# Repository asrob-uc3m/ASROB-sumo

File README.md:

# ASROB-sumo
Robot sumo de RoboFactory

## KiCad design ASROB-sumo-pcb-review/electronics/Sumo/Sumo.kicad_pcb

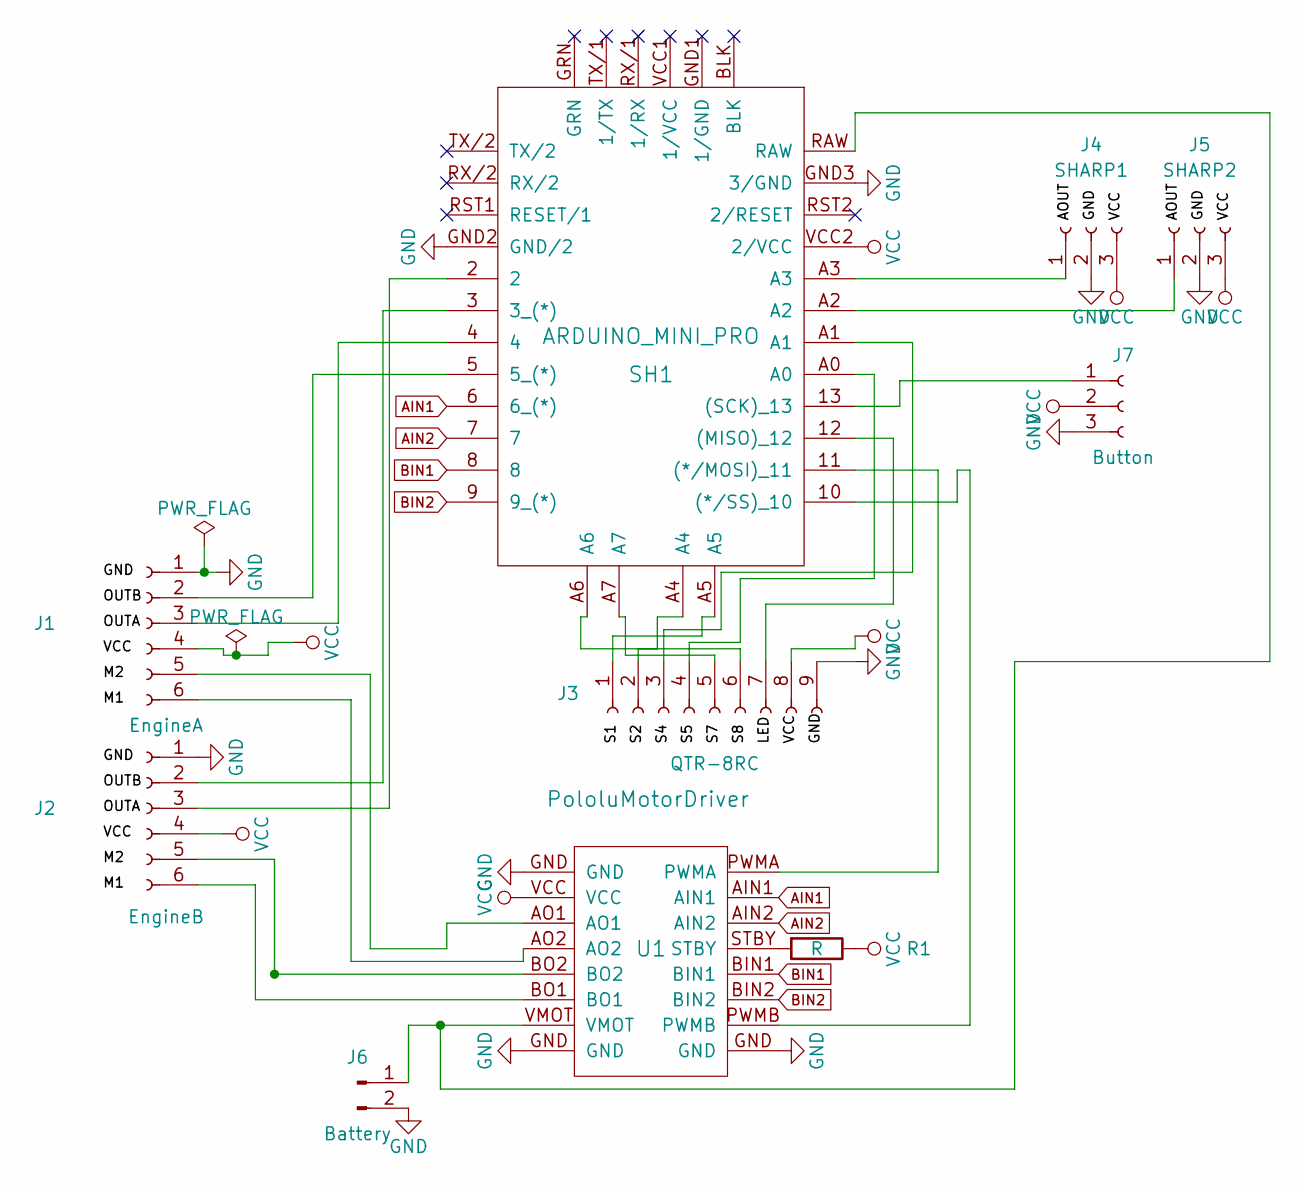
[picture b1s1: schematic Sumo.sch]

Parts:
J1: EngineA; Socket_Strip_Straight_1x06_Pitch2.54mm
J2: EngineB; Socket_Strip_Straight_1x06_Pitch2.54mm
J3: QTR-8RC; Socket_Strip_Straight_1x09_Pitch2.54mm
J4: SHARP1; Socket_Strip_Straight_1x03_Pitch2.54mm
J5: SHARP2; Socket_Strip_Straight_1x03_Pitch2.54mm
J6: Battery; Pin_Header_Straight_1x02_Pitch2.54mm
J7: Button; Socket_Strip_Straight_1x03_Pitch2.54mm
R1: R; R_Axial_DIN0204_L3.6mm_D1.6mm_P5.08mm_Horizontal
SH1: ARDUINO_MINI_PRO; ARDUINO_MINI_PRO_V10
U1: PololuMotorDriver

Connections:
AIN1: SH1.6 (6_(*)), U1.AIN1
AIN2: SH1.7, U1.AIN2
BIN1: SH1.8, U1.BIN1
BIN2: SH1.9 (9_(*)), U1.BIN2
GND: J1.1, J2.1, J3.9, J4.2, J5.2, J6.2, J7.3, SH1.GND2 (GND/2), SH1.GND3 (3/GND), U1.GND
unnamed: J1.2, SH1.5 (5_(*))
unnamed: J1.3, SH1.4
unnamed: J1.5, U1.AO1
unnamed: J1.6, U1.AO2
unnamed: J2.2, SH1.3 (3_(*))
unnamed: J2.3, SH1.2
unnamed: J2.5, U1.BO2
unnamed: J2.6, U1.BO1
unnamed: J3.1, SH1.A5
unnamed: J3.2, SH1.A4
unnamed: J3.3, SH1.A1
unnamed: J3.4, SH1.A0
unnamed: J3.5, SH1.A7
unnamed: J3.6, SH1.A6
unnamed: J3.7, SH1.12 ((MISO)_12)
unnamed: J4.1, SH1.A3
unnamed: J5.1, SH1.A2
unnamed: J6.1, SH1.RAW, U1.VMOT
unnamed: J7.1, SH1.13 ((SCK)_13)
unnamed: R1.2, U1.STBY
unnamed: SH1.10 ((*/SS)_10), U1.PWMB
unnamed: SH1.11 ((*/MOSI)_11), U1.PWMA
VCC: J1.4, J2.4, J3.8, J4.3, J5.3, J7.2, R1.1, SH1.VCC2 (2/VCC), U1.VCC

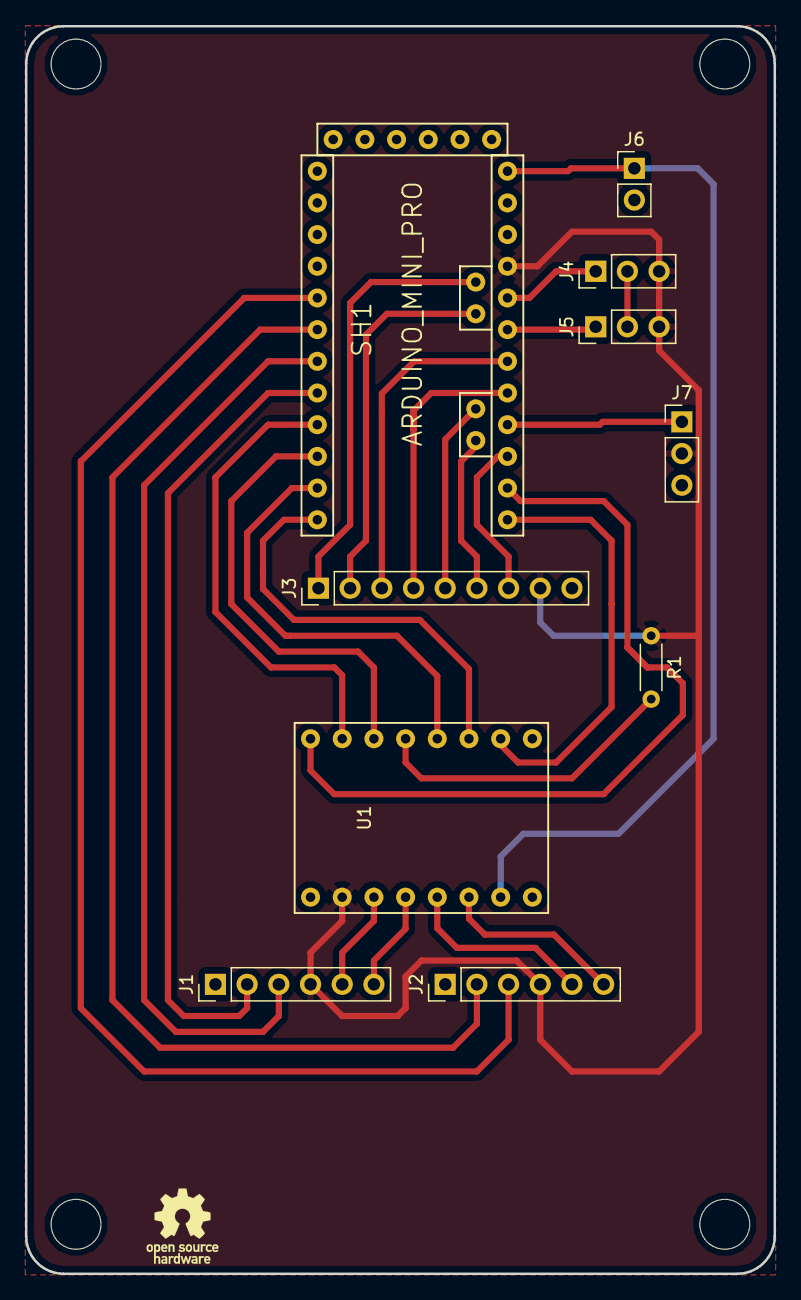
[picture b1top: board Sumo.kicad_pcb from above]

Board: 2 copper layers, 60.0 x 100.0 mm, 10 parts (0 on the bottom side), 28 nets.

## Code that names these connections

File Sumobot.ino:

#include <QTRSensors.h>
#define NUM_SENSORS 4
#define TIMEOUT 2500
#define EMITTER_PIN 8

QTRSensorsRC qtrrc((unsigned char[]) {A4, A3, A2, A1},
  NUM_SENSORS, TIMEOUT, EMITTER_PIN); 
unsigned int sensorValues[NUM_SENSORS];

int SH1 = A0;
int SH2 = A5;
int QTR1 = A1;
int QTR4 = A2;
int QTR5 = A3;
int QTR8 = A4;
int Bin1 = 5;
int Bin2 = 6;
int Ain1 = 11;
int Ain2 = 12;
int PwmA = 10;
int PwmB = 9;
int Button = 7;

void setup() {
  delay(500);
  pinMode(13, OUTPUT);
  digitalWrite(13, HIGH);
  for (int i = 0; i < 200; i++) 
  {
    qtrrc.calibrate();
  }
  digitalWrite(13, LOW);
  
  pinMode(Button, INPUT);
  pinMode(Bin1, OUTPUT);
  pinMode(Bin2, OUTPUT);
  pinMode(Ain1, OUTPUT);
  pinMode(Ain2, OUTPUT);
  pinMode(PwmA, OUTPUT);
  pinMode(PwmB, OUTPUT);
  Serial.begin(9600);
}
void loop() {
  int a=0, detect=0;
  if(digitalRead(Button)==LOW){
    a=1;
    delay(1000);//The delay before starting the programme, takes value 5000 in the final version
  }
  while(a==1){
    delay(1000);
    unsigned int place = qtrrc.readLine(sensorValues);
    int D1=0;
    int D2=0;
    for(int i=0; i<10; i++){
      D1=D1+analogRead(SH1);
      D2=D2+analogRead(SH2);
    }
    D1=D1/10;
    D2=D2/10;
    /*Serial.print(D1);
    Serial.print('\t');
    Serial.print(D2);
    for(int i=0;i<NUM_SENSORS;i++){
      Serial.print('\t');
      Serial.print(sensorValues[i]);
    }
    Serial.println();
    This is just to print in the serial monitor the values of the sharp sensors and the QTR's*/
    if(D1<150&&D2<150){
      spin();
    }
    else if(D1>=150&&D2>=300){
      forth();
    }
    else if(D1>=150){
      turn_left_fast();
      delay(50);
    }
    else if(D2>=150){
      turn_right_fast();
      delay(50);
    }
    /*else if(sensorValues[0]<Value&&sensorValues[3]){
     * back();
     * delay(500);
     * turn_left();
     * delay(500);
     * }
     * else if(sensorValues[0]<Value){
     *   turn_left();
     *   delay(500);
     * }
     * else if(sensorValues[3]<Value){
     *   turn_right();
     *   delay(500);
     * }
     */
  }
}

void no_motion(){
      analogWrite(PwmA, 0);
      analogWrite(PwmB, 0);
      digitalWrite(Ain1, LOW);
      digitalWrite(Ain2, LOW);
      digitalWrite(Bin1, LOW);
      digitalWrite(Bin2, LOW);
}
void fast_detention(){
      analogWrite(PwmA, 0);
      analogWrite(PwmB, 0);
      digitalWrite(Ain1, HIGH);
      digitalWrite(Ain2, HIGH);
      digitalWrite(Bin1, HIGH);
      digitalWrite(Bin2, HIGH);
}
void forth(){
      analogWrite(PwmA, 230);
      analogWrite(PwmB, 230);
      digitalWrite(Ain1, HIGH);
      digitalWrite(Ain2, LOW);
      digitalWrite(Bin1, HIGH);
      digitalWrite(Bin2, LOW);
}
void back(){
      analogWrite(PwmA, 200);
      analogWrite(PwmB, 200);
      digitalWrite(Ain1, LOW);
      digitalWrite(Ain2, HIGH);
      digitalWrite(Bin1, LOW);
      digitalWrite(Bin2, HIGH);
}
void turn_left_fast(){
      analogWrite(PwmA, 230);
      analogWrite(PwmB, 180);
      digitalWrite(Ain1, HIGH);
      digitalWrite(Ain2, LOW);
      digitalWrite(Bin1, HIGH);
      digitalWrite(Bin2, LOW);
}
void turn_right_fast(){
      analogWrite(PwmA, 180);
      analogWrite(PwmB, 230);
      digitalWrite(Ain1, HIGH);
      digitalWrite(Ain2, LOW);
      digitalWrite(Bin1, HIGH);
      digitalWrite(Bin2, LOW);
}
void spin(){
      analogWrite(PwmA, 230);
      analogWrite(PwmB, 50);
      digitalWrite(Ain1, HIGH);
      digitalWrite(Ain2, LOW);
      digitalWrite(Bin1, HIGH);
      digitalWrite(Bin2, LOW);
}
void turn_left(){
      analogWrite(PwmA, 150);
      analogWrite(PwmB, 50);
      digitalWrite(Ain1, LOW);
      digitalWrite(Ain2, HIGH);
      digitalWrite(Bin1, HIGH);
      digitalWrite(Bin2, LOW);
}
void turn_right(){
      analogWrite(PwmA, 50);
      analogWrite(PwmB, 150);
      digitalWrite(Ain1, HIGH);
      digitalWrite(Ain2, LOW);
      digitalWrite(Bin1, LOW);
      digitalWrite(Bin2, HIGH);
}
void turn_left_back(){
      analogWrite(PwmA, 50);
      analogWrite(PwmB, 150);
      digitalWrite(Ain1, LOW);
      digitalWrite(Ain2, HIGH);
      digitalWrite(Bin1, LOW);
      digitalWrite(Bin2, HIGH);
}
void turn_right_back(){
      analogWrite(PwmA, 150);
      analogWrite(PwmB, 50);
      digitalWrite(Ain1, LOW);
      digitalWrite(Ain2, HIGH);
      digitalWrite(Bin1, LOW);
      digitalWrite(Bin2, HIGH);
}

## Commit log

2017-11-22 Primer diseño de piezas en 3D
    Primer diseño 3D de algunas de las pieza del sumo, algunas de las cuales necesitan ser impresas como chasis del robot. Resubiré los modelos acabados y el modelo ensamblado más adelante.
2017-12-03 Nueva version 3D de las partes para imprimir
    Version (esperemos) definitiva de las partes para imprimir del sumo y el ensamblaje, una de las piezas de la estructura es distinta al ensamblaje, pero este último es para hacerse una idea del result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
2018-02-03 Imprimibles
    Ficheros en formato STL de las distintas piezas para imprimir, modificadas para dejar algo de margen a la impresora 3d en los distintos huecos para tornillos, tuercas y el eje del motor.
2018-03-14 Alpha version
    La versión inicial del codigo del sumo, contiene las funciones de movimiento, el calibrado de los sensores y la asignación de los pines, que es la parte más tediosa. Subido para que lo vayan mjorando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
2018-03-15 PCB test funcionalidad
    Esquema de PCB aleatorio para solucionar problemas kicad
2018-04-10 Nueva version chasis
    Segunda versión del chasis del sumo, más "apta" para impresión que la primera.
2018-04-15 Versión revisión PCB
    Primera versión de la PCB lista para revisión, todos los archivos se encuentran en el archivo ZIP.
2018-04-24 Nueva versión de la PCB
    Nueva versión de la PCB con la mayoría de los cambios que hemos comentado en las reuniones, taladros, finalización de la región de cobre para el gnd, algunas conexiones sueltas y el nombre del robot 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
2018-05-03 Limpiar el repo
2018-05-03 PCB v-final
    Última versión (esperemos) de la placa, como en la versión anterior, solo queda introducir el logo y encargarla
2018-05-06 Add files to control version
2018-05-06 Fix traces, add rounded edges, add mounting holes
2018-05-06 Add logo component
2018-05-06 Add logo to PCB
2018-05-14 Nueva versión PCB
    Tras revisar una última vez la placa antes de imprimirla, hemos detectado un par de errores de cierta importancia:
    -El primero de ellos era la falta de una conexión para las baterias que se han de conectar en el puerto correspondiente de la arduino, no como estaba antes y en la conexión correspondiente del puente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
    -El segundo era la falta de una conexión para el botón de puesta en marcha del robot.
    Ambos fallos han sido solventados sin ningún problema y quedan a la espera de aprobación.
2018-10-18 Updated and organized hardware
    New versions of the sumo components have been included. New wheel prevents the shaft from slipping, the base has new holes for attaching the PCB and the SHARP sensors in a beter position, and the eng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
    New organization of the differentt version, including printables has been done.
